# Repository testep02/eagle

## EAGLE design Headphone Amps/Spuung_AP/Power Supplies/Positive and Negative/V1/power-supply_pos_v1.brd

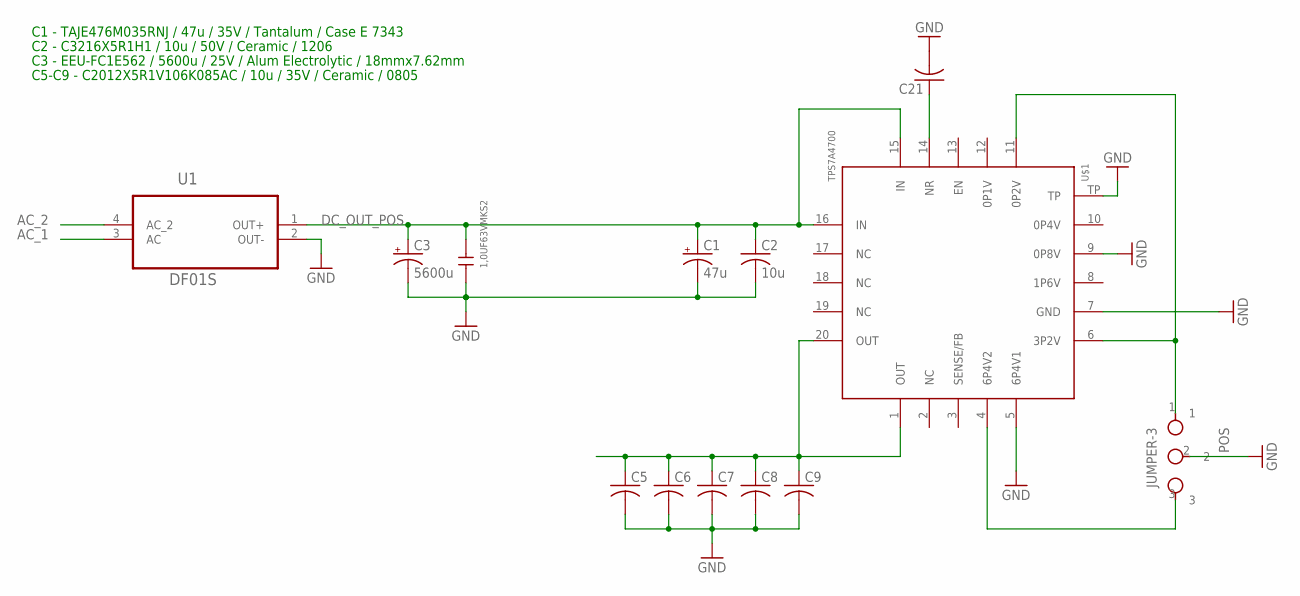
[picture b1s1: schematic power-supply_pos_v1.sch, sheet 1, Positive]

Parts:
C1: 47u; SMC_E
C2: 10u; C1206
C3: 5600u; E7,5-18
C4: 1,0UF63VMKS2; 5,0X10,0RM5,0
C5, C6, C7, C8, C9: C-USC0805; C0805
C21: C-USC0603; C0603
POS: JUMPER-3; 1X03
U1: DF01S; SOT508P985X260-4N
U$1: TPS7A4700; VQFN-20

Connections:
AC_1: U1.3 (AC)
AC_2: U1.4 (AC_2)
DC_OUT_POS: C1.+, C2.1, C3.+, C4.2, U1.1 (OUT+), U$1.15 (IN), U$1.16 (IN)
GND: C1.-, C2.2, C3.-, C4.1, C5.2, C6.2, C7.2, C8.2, C9.2, C21.2, POS.2, U1.2 (OUT-), U$1.5 (6P4V1), U$1.7 (GND), U$1.9 (0P8V), U$1.TP; also elsewhere on the board
unnamed: POS.3, U$1.4 (6P4V2)
unnamed: POS.1, U$1.6 (3P2V), U$1.11 (0P2V)
unnamed: C21.1, U$1.14 (NR)
POS_OUT: C5.1, C6.1, C7.1, C8.1, C9.1, U$1.1 (OUT), U$1.20 (OUT)

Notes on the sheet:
C1 - TAJE476M035RNJ / 47u / 35V / Tantalum / Case E 7343
C2 - C3216X5R1H1 / 10u / 50V / Ceramic / 1206
C3 - EEU-FC1E562 / 5600u / 25V / Alum Electrolytic / 18mmx7.62mm
C5-C9 - C2012X5R1V106K085AC / 10u / 35V / Ceramic / 0805

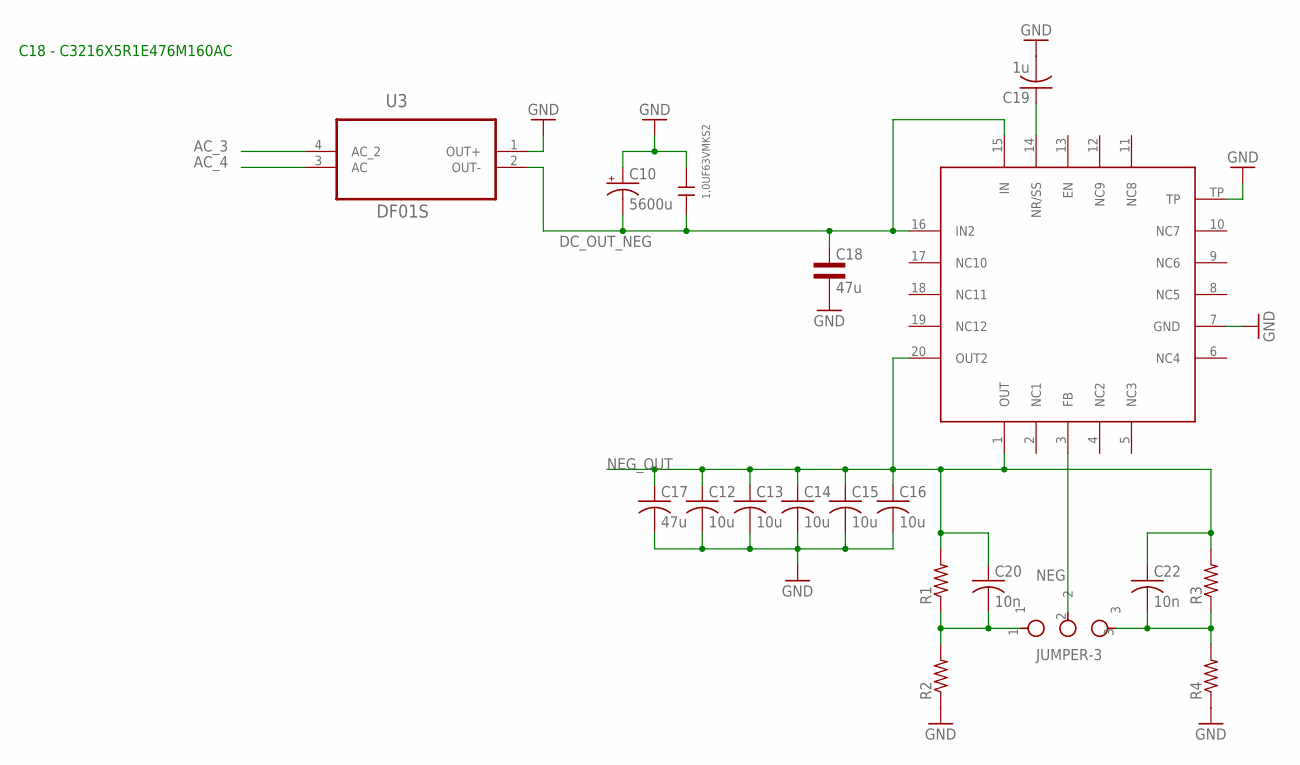
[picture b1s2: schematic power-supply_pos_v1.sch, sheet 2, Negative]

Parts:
C10: 5600u; E7,5-18
C11: 1,0UF63VMKS2; 5,0X10,0RM5,0
C12, C13, C14, C15, C16: 10u; C0805
C17: 47u; C2220K
C18: 47u; 1206L3
C19: 1u; C0603
C20, C22: 10n; C0603
NEG: JUMPER-3; 1X03
R1, R2, R3, R4: R-US_R0603; R0603
U3: DF01S; SOT508P985X260-4N
U$2: TPS7A3301RGWT; VQFN-20

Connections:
AC_3: U3.4 (AC_2)
AC_4: U3.3 (AC)
DC_OUT_NEG: C10.-, C11.1, C18.1, U3.2 (OUT-), U$2.15 (IN), U$2.16 (IN2)
GND: C10.+, C11.2, C12.2, C13.2, C14.2, C15.2, C16.2, C17.2, C18.2, C19.2, R2.1, R4.1, U3.1 (OUT+), U$2.7 (GND), U$2.TP; also elsewhere on the board
unnamed: C20.2, NEG.1, R1.1, R2.2
unnamed: C19.1, U$2.14 (NR/SS)
unnamed: C22.2, NEG.3, R3.1, R4.2
unnamed: NEG.2, U$2.3 (FB)
NEG_OUT: C12.1, C13.1, C14.1, C15.1, C16.1, C17.1, C20.1, C22.1, R1.2, R3.2, U$2.1 (OUT), U$2.20 (OUT2)

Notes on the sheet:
C18 - C3216X5R1E476M160AC

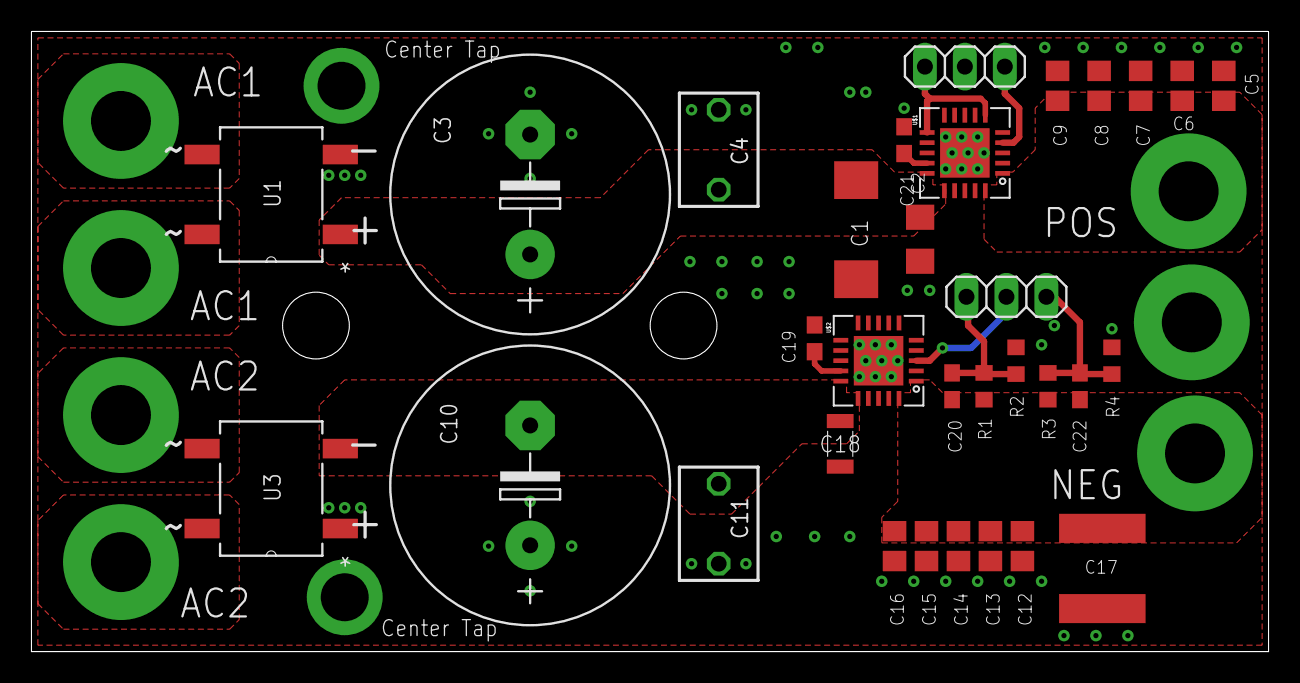
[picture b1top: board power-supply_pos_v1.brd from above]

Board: 2 copper layers, 78.6 x 39.4 mm, 32 parts (0 on the bottom side), 12 nets.

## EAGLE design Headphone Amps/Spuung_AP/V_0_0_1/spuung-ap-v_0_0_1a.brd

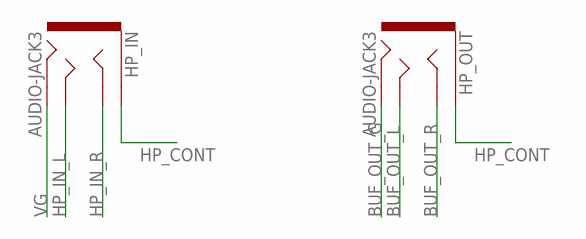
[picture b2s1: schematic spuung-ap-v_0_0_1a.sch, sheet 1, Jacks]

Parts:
HP_IN: AUDIO-JACK3; AUDIO-JACK-TRRS-SMD
HP_OUT: AUDIO-JACK3; AUDIO-JACK-TRRS-SMD

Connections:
BUF_OUT_G: HP_OUT.RING2
BUF_OUT_L: HP_OUT.TIP; also elsewhere on the board
BUF_OUT_R: HP_OUT.RING1; also elsewhere on the board
HP_CONT: HP_IN.EARTH, HP_OUT.EARTH
HP_IN_L: HP_IN.TIP; also elsewhere on the board
HP_IN_R: HP_IN.RING1; also elsewhere on the board
VG: HP_IN.RING2; also elsewhere on the board

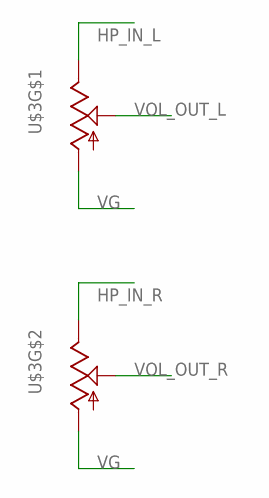
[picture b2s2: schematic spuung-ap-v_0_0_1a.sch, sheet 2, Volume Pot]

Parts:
U$3: ALPS_BLUE; ALPS_RK27

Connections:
HP_IN_L: U$3.I1 (3); also elsewhere on the board
HP_IN_R: U$3.I2 (3); also elsewhere on the board
VG: U$3.G1 (1), U$3.G2 (1); also elsewhere on the board
VOL_OUT_L: U$3.O1 (2); also elsewhere on the board
VOL_OUT_R: U$3.O2 (2); also elsewhere on the board

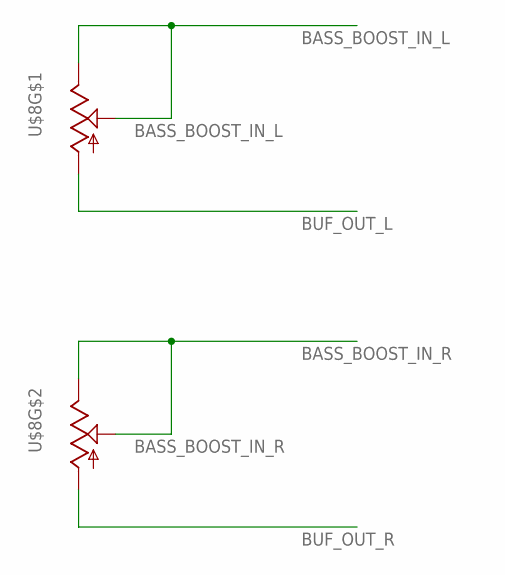
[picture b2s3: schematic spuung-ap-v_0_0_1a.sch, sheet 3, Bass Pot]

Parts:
U$8: ALPS_BLUE; ALPS_RK27

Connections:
BASS_BOOST_IN_L: U$8.I1 (3), U$8.O1 (2); also elsewhere on the board
BASS_BOOST_IN_R: U$8.I2 (3), U$8.O2 (2); also elsewhere on the board
BUF_OUT_L: U$8.G1 (1); also elsewhere on the board
BUF_OUT_R: U$8.G2 (1); also elsewhere on the board

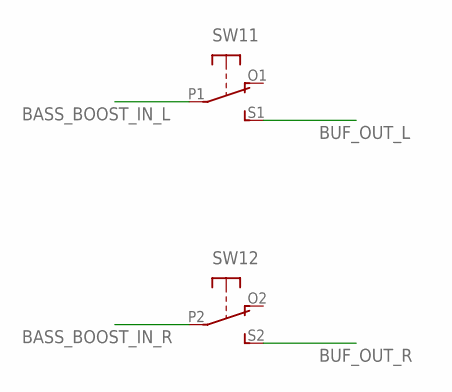
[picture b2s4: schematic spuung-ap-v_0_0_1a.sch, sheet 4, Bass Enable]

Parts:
SW1: DPDT-EG1390; EG1390

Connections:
BASS_BOOST_IN_L: SW1.P1; also elsewhere on the board
BASS_BOOST_IN_R: SW1.P2; also elsewhere on the board
BUF_OUT_L: SW1.S1 (S); also elsewhere on the board
BUF_OUT_R: SW1.S2 (S); also elsewhere on the board

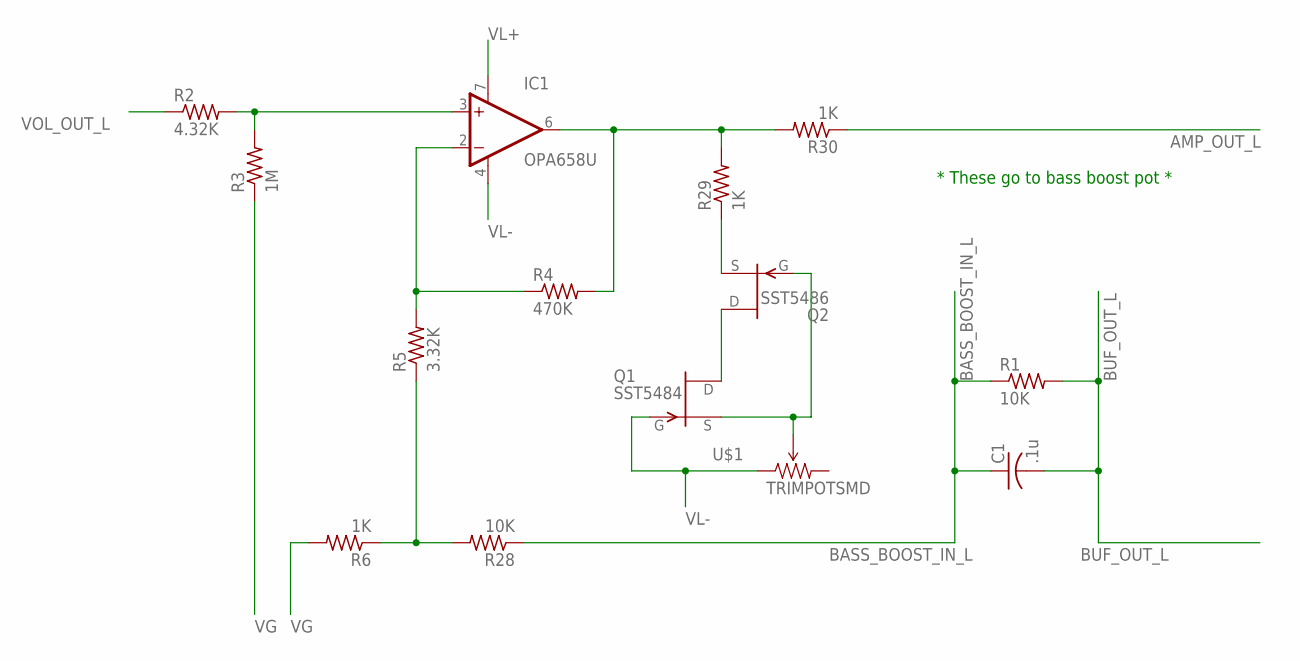
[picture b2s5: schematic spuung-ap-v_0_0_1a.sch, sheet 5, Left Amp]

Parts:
C1: .1u; C0805
IC1: OPA658U; SO08
Q1: SST5484; SOT23
Q2: SST5486; SOT23
R1, R28: 10K; R0805
R2: 4.32K; R0805
R3: 1M; R0805
R4: 470K; R0805
R5: 3.32K; R0805
R6, R29, R30: 1K; R0805
U$1: TRIMPOTSMD; TRIMPOT-3MM

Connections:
AMP_OUT_L: R30.1
BASS_BOOST_IN_L: C1.1, R1.1, R28.1; also elsewhere on the board
BUF_OUT_L: C1.2, R1.2; also elsewhere on the board
unnamed: Q2.2 (S), R29.1
unnamed: IC1.3 (+IN), R2.2, R3.2
unnamed: IC1.2 (-IN), R4.1, R5.2
unnamed: Q1.1 (D), Q2.1 (D)
unnamed: Q1.2 (S), Q2.3 (G), U$1.2 (WIPER)
unnamed: IC1.6 (OUT), R4.2, R29.2, R30.2
unnamed: R5.1, R6.1, R28.2
VG: R3.1, R6.2; also elsewhere on the board
VL+: IC1.7 (V+)
VL-: IC1.4 (V-), Q1.3 (G), U$1.1 (CCW)
VOL_OUT_L: R2.1; also elsewhere on the board

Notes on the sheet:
* These go to bass boost pot *

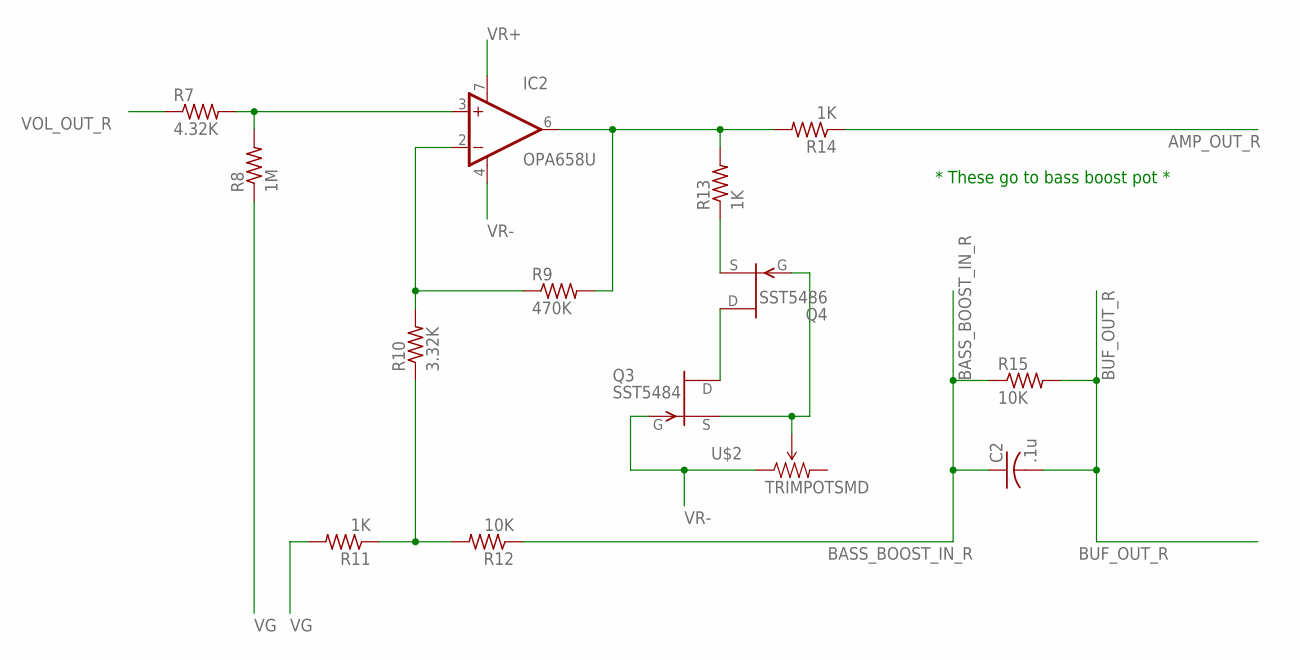
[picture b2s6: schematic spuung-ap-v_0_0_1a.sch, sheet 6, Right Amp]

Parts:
C2: .1u; C0805
IC2: OPA658U; SO08
Q3: SST5484; SOT23
Q4: SST5486; SOT23
R7: 4.32K; R0805
R8: 1M; R0805
R9: 470K; R0805
R10: 3.32K; R0805
R11, R13, R14: 1K; R0805
R12, R15: 10K; R0805
U$2: TRIMPOTSMD; TRIMPOT-3MM

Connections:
AMP_OUT_R: R14.1
BASS_BOOST_IN_R: C2.1, R12.1, R15.1; also elsewhere on the board
BUF_OUT_R: C2.2, R15.2; also elsewhere on the board
unnamed: IC2.3 (+IN), R7.2, R8.2
unnamed: IC2.2 (-IN), R9.1, R10.2
unnamed: IC2.6 (OUT), R9.2, R13.2, R14.2
unnamed: R10.1, R11.1, R12.2
unnamed: Q4.2 (S), R13.1
unnamed: Q3.1 (D), Q4.1 (D)
unnamed: Q3.2 (S), Q4.3 (G), U$2.2 (WIPER)
VG: R8.1, R11.2; also elsewhere on the board
VOL_OUT_R: R7.1; also elsewhere on the board
VR+: IC2.7 (V+)
VR-: IC2.4 (V-), Q3.3 (G), U$2.1 (CCW)

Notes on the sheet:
* These go to bass boost pot *

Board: 2 copper layers, 33 parts (0 on the bottom side), 26 nets, no tracks yet.

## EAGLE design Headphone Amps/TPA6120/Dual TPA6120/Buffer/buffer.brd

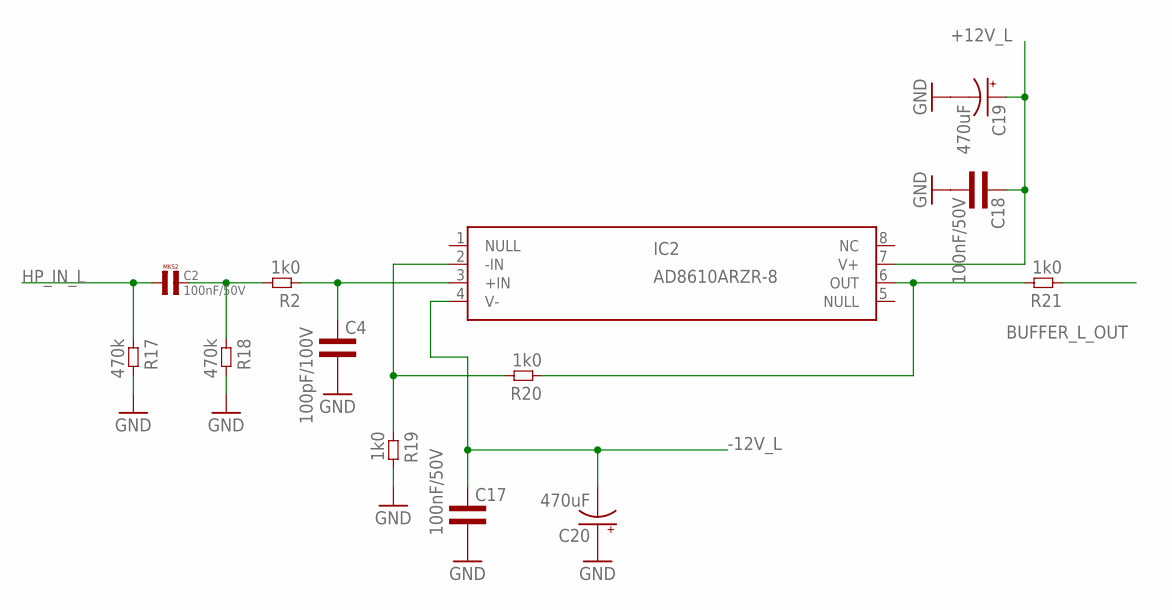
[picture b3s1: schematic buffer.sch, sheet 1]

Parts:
C2: 100nF/50V; R5B3
C4: 100pF/100V; 0603L3
C17, C18: 100nF/50V; 0603L3
C19, C20: 470uF; E3,5-8
IC2: AD8610ARZR-8; 8-LEAD-SOIC_N
R2, R19, R20, R21: 1k0; 0603L3
R17, R18: 470k; 0603L3

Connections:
+12V_L: C18.P$1 (1), C19.+, IC2.7 (V+); also elsewhere on the board
-12V_L: C17.P$1 (1), C20.-, IC2.4 (V-); also elsewhere on the board
BUFFER_L_OUT: IC2.6 (OUT), R20.P$1 (1), R21.P$2 (2)
BUFF_L_OUT: R21.P$1 (1); also elsewhere on the board
GND: C4.P$2 (2), C17.P$2 (2), C18.P$2 (2), C19.-, C20.+, R17.P$2 (2), R18.P$2 (2), R19.P$2 (2); also elsewhere on the board
HP_IN_L: C2.1, R17.P$1 (1); also elsewhere on the board
unnamed: C2.2, R2.P$2 (2), R18.P$1 (1)
unnamed: C4.P$1 (1), IC2.3 (+IN), R2.P$1 (1)
unnamed: IC2.2 (-IN), R19.P$1 (1), R20.P$2 (2)

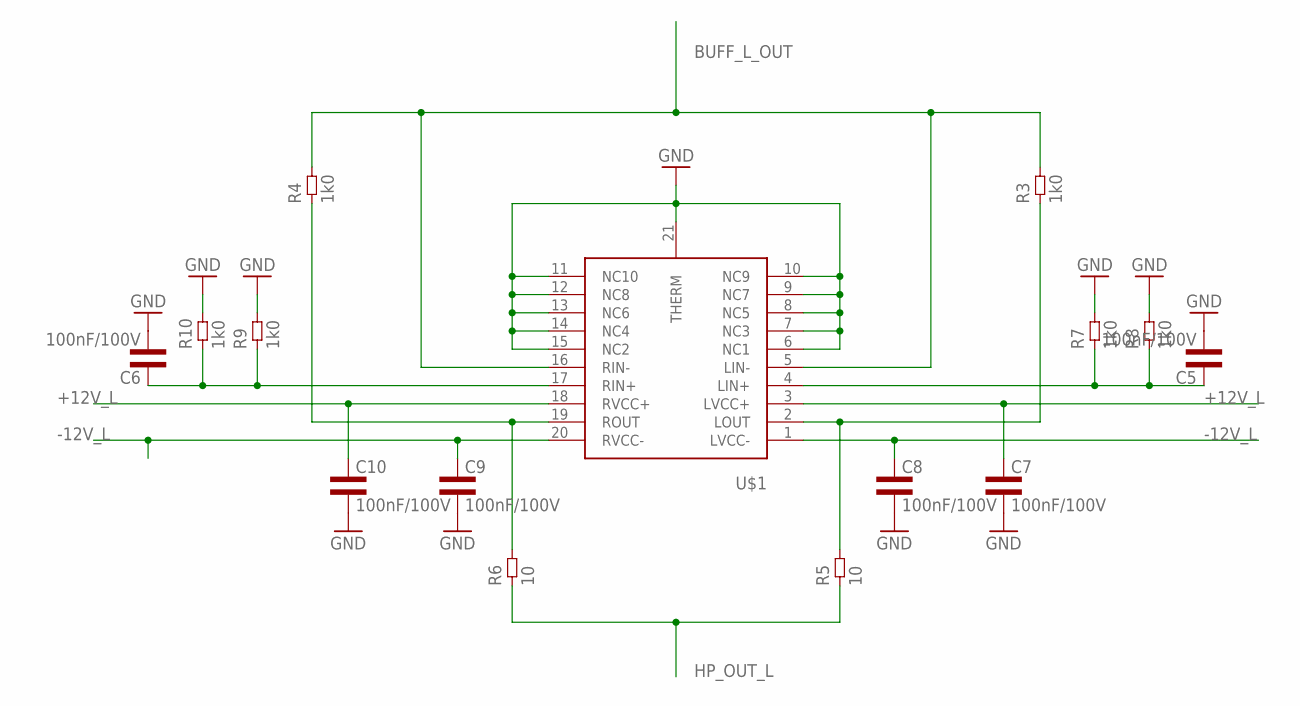
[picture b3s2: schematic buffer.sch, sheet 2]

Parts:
C5, C6: 100nF/100V; 0603L3
C7, C8, C9, C10: 100nF/100V; 0805L3
R3, R4, R7, R8, R9, R10: 1k0; 0603L3
R5, R6: 10; 1210L3
U$1: TPA6120_TPA6120

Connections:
+12V_L: C7.1, C10.1, U$1.3 (LVCC+), U$1.18 (RVCC+); also elsewhere on the board
-12V_L: C8.1, C9.1, U$1.1 (LVCC-), U$1.20 (RVCC-); also elsewhere on the board
BUFF_L_OUT: R3.P$2 (2), R4.P$2 (2), U$1.5 (LIN-), U$1.16 (RIN-); also elsewhere on the board
GND: C5.P$2 (2), C6.P$2 (2), C7.2, C8.2, C9.2, C10.2, R7.P$2 (2), R8.P$2 (2), R9.P$2 (2), R10.P$2 (2), U$1.6 (NC1), U$1.7 (NC3), U$1.8 (NC5), U$1.9 (NC7), U$1.10 (NC9), U$1.11 (NC10), U$1.12 (NC8), U$1.13 (NC6), U$1.14 (NC4), U$1.15 (NC2), U$1.21 (THERM); also elsewhere on the board
HP_OUT_L: R5.P$1 (1), R6.P$1 (1); also elsewhere on the board
unnamed: C5.P$1 (1), R7.P$1 (1), R8.P$1 (1), U$1.4 (LIN+)
unnamed: C6.P$1 (1), R9.P$1 (1), R10.P$1 (1), U$1.17 (RIN+)
OUT_L: R3.P$1 (1), R5.P$2 (2), U$1.2 (LOUT)
OUT_R: R4.P$1 (1), R6.P$2 (2), U$1.19 (ROUT)

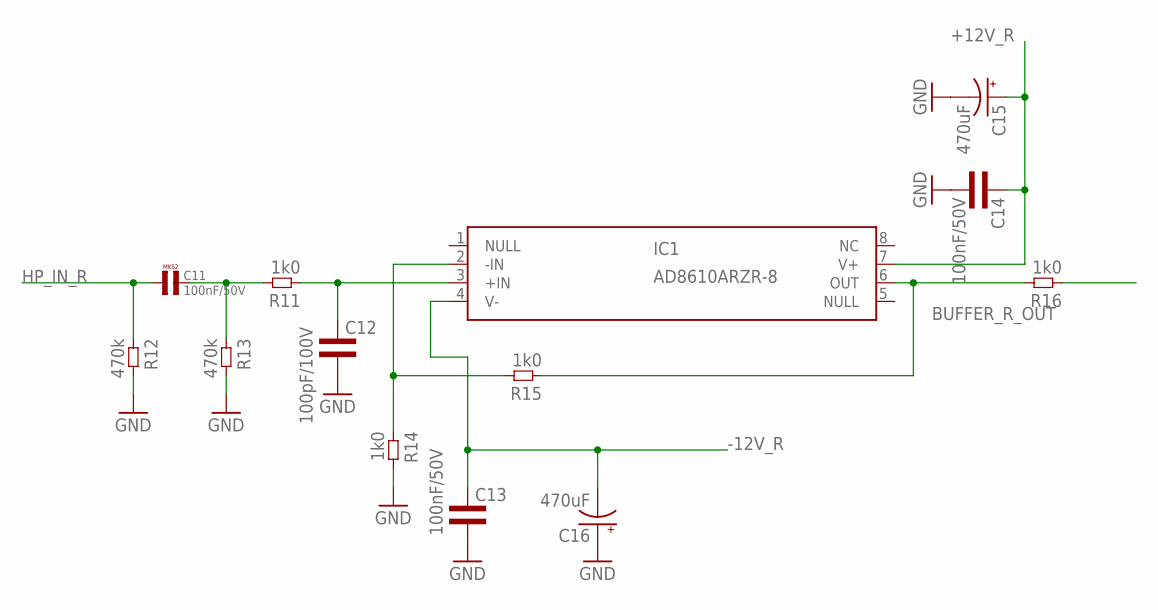
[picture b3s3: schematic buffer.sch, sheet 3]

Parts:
C11: 100nF/50V; R5B3
C12: 100pF/100V; 0603L3
C13, C14: 100nF/50V; 0603L3
C15, C16: 470uF; E3,5-8
IC1: AD8610ARZR-8; 8-LEAD-SOIC_N
R11, R14, R15, R16: 1k0; 0603L3
R12, R13: 470k; 0603L3

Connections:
+12V_R: C14.P$1 (1), C15.+, IC1.7 (V+); also elsewhere on the board
-12V_R: C13.P$1 (1), C16.-, IC1.4 (V-); also elsewhere on the board
BUFFER_R_OUT: IC1.6 (OUT), R15.P$1 (1), R16.P$2 (2)
BUFF_R_OUT: R16.P$1 (1); also elsewhere on the board
GND: C12.P$2 (2), C13.P$2 (2), C14.P$2 (2), C15.-, C16.+, R12.P$2 (2), R13.P$2 (2), R14.P$2 (2); also elsewhere on the board
HP_IN_R: C11.1, R12.P$1 (1); also elsewhere on the board
unnamed: C11.2, R11.P$2 (2), R13.P$1 (1)
unnamed: C12.P$1 (1), IC1.3 (+IN), R11.P$1 (1)
unnamed: IC1.2 (-IN), R14.P$1 (1), R15.P$2 (2)

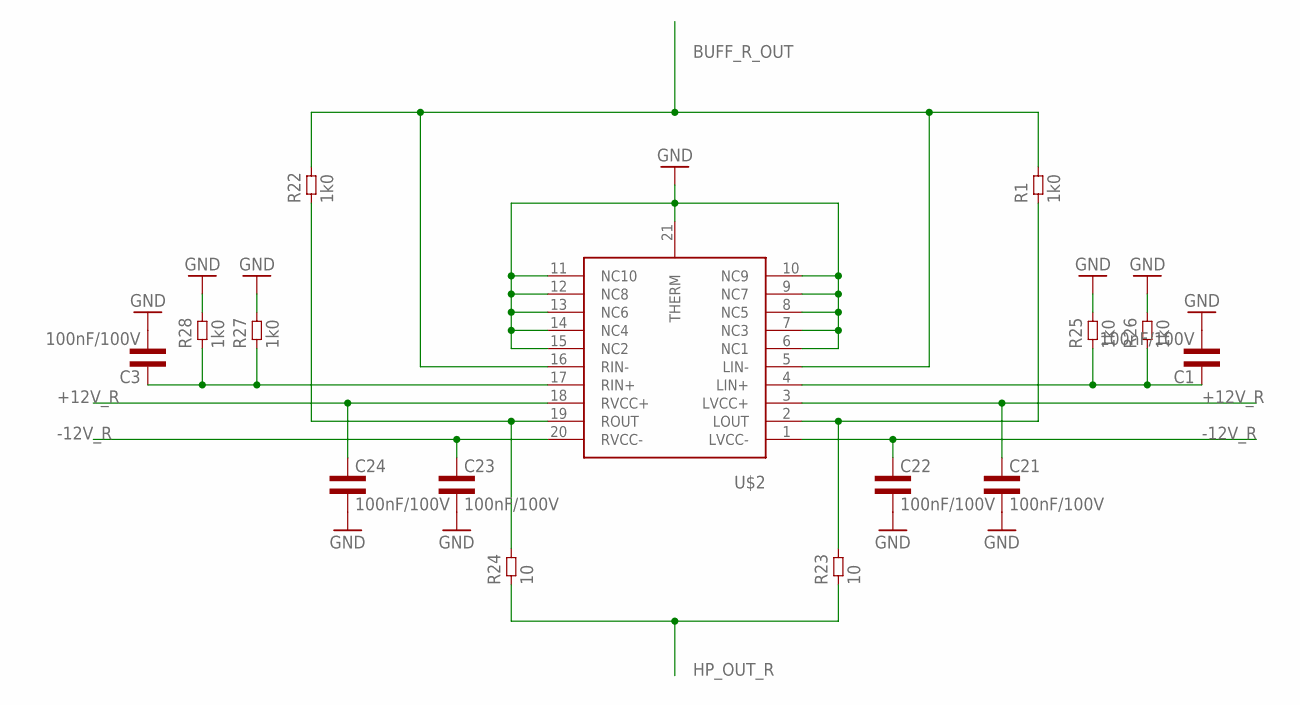
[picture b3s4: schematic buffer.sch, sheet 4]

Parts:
C1, C3: 100nF/100V; 0603L3
C21, C22, C23, C24: 100nF/100V; 0805L3
R1, R22, R25, R26, R27, R28: 1k0; 0603L3
R23, R24: 10; 1210L3
U$2: TPA6120_TPA6120

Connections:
+12V_R: C21.1, C24.1, U$2.3 (LVCC+), U$2.18 (RVCC+); also elsewhere on the board
-12V_R: C22.1, C23.1, U$2.1 (LVCC-), U$2.20 (RVCC-); also elsewhere on the board
BUFF_R_OUT: R1.P$2 (2), R22.P$2 (2), U$2.5 (LIN-), U$2.16 (RIN-); also elsewhere on the board
GND: C1.P$2 (2), C3.P$2 (2), C21.2, C22.2, C23.2, C24.2, R25.P$2 (2), R26.P$2 (2), R27.P$2 (2), R28.P$2 (2), U$2.6 (NC1), U$2.7 (NC3), U$2.8 (NC5), U$2.9 (NC7), U$2.10 (NC9), U$2.11 (NC10), U$2.12 (NC8), U$2.13 (NC6), U$2.14 (NC4), U$2.15 (NC2), U$2.21 (THERM); also elsewhere on the board
HP_OUT_R: R23.P$1 (1), R24.P$1 (1); also elsewhere on the board
unnamed: C1.P$1 (1), R25.P$1 (1), R26.P$1 (1), U$2.4 (LIN+)
unnamed: C3.P$1 (1), R27.P$1 (1), R28.P$1 (1), U$2.17 (RIN+)
OUT_L1: R1.P$1 (1), R23.P$2 (2), U$2.2 (LOUT)
OUT_R1: R22.P$1 (1), R24.P$2 (2), U$2.19 (ROUT)

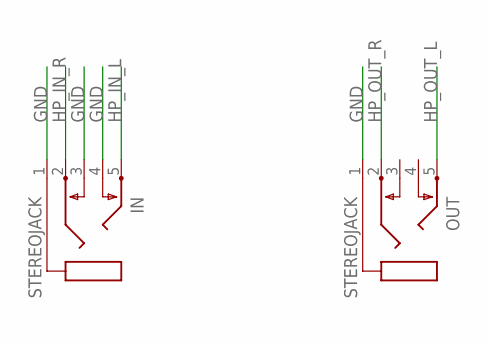
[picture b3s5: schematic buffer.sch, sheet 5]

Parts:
IN: STEREOJACK; STX3100
OUT: STEREOJACK; STX3100

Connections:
GND: IN.1, IN.3, IN.4, OUT.1; also elsewhere on the board
HP_IN_L: IN.5; also elsewhere on the board
HP_IN_R: IN.2; also elsewhere on the board
HP_OUT_L: OUT.5; also elsewhere on the board
HP_OUT_R: OUT.2; also elsewhere on the board

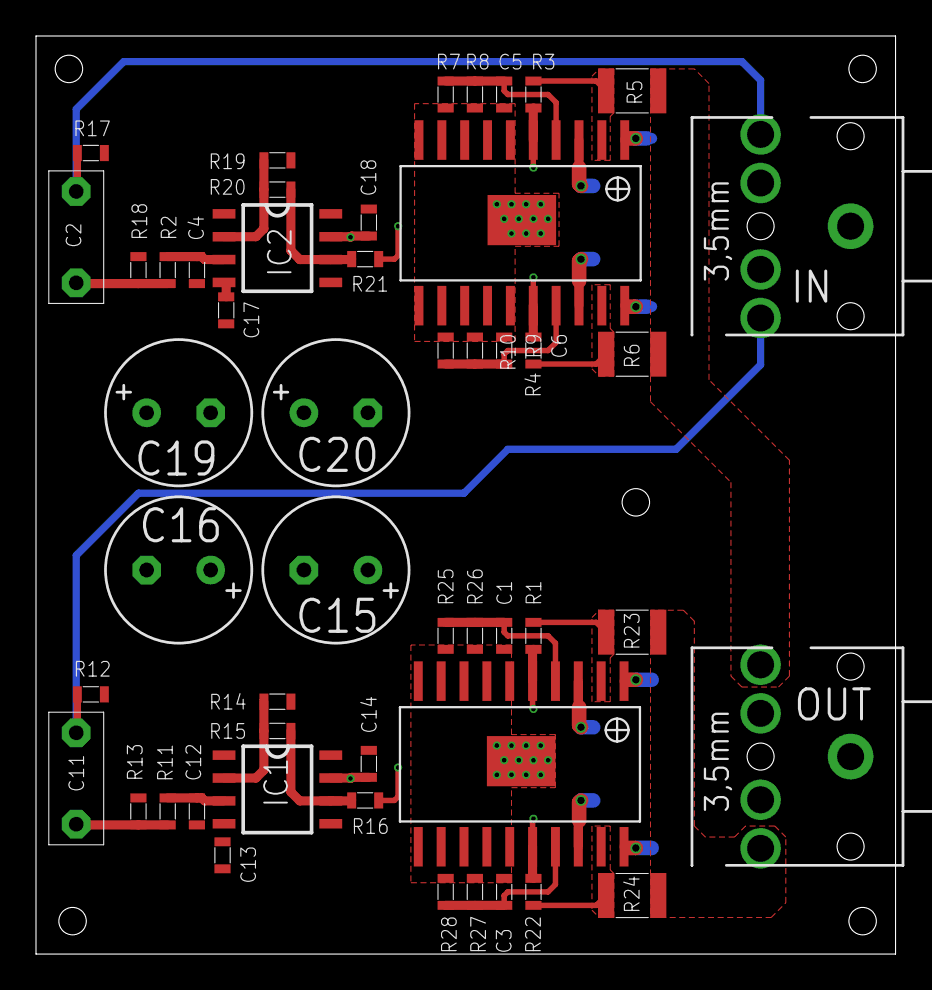
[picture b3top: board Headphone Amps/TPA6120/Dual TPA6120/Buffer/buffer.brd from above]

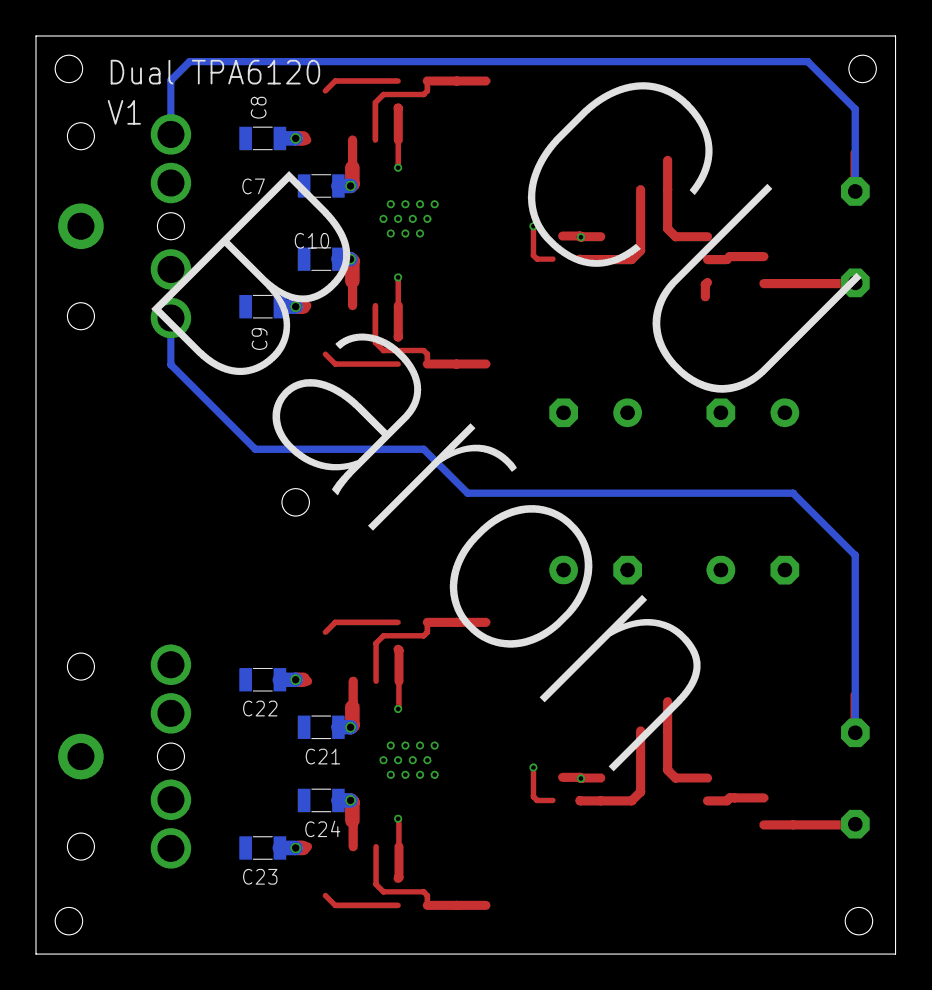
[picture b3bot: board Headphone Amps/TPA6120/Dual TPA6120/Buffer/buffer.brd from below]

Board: 4 copper layers, 47.8 x 51.0 mm, 58 parts (8 on the bottom side), 27 nets.

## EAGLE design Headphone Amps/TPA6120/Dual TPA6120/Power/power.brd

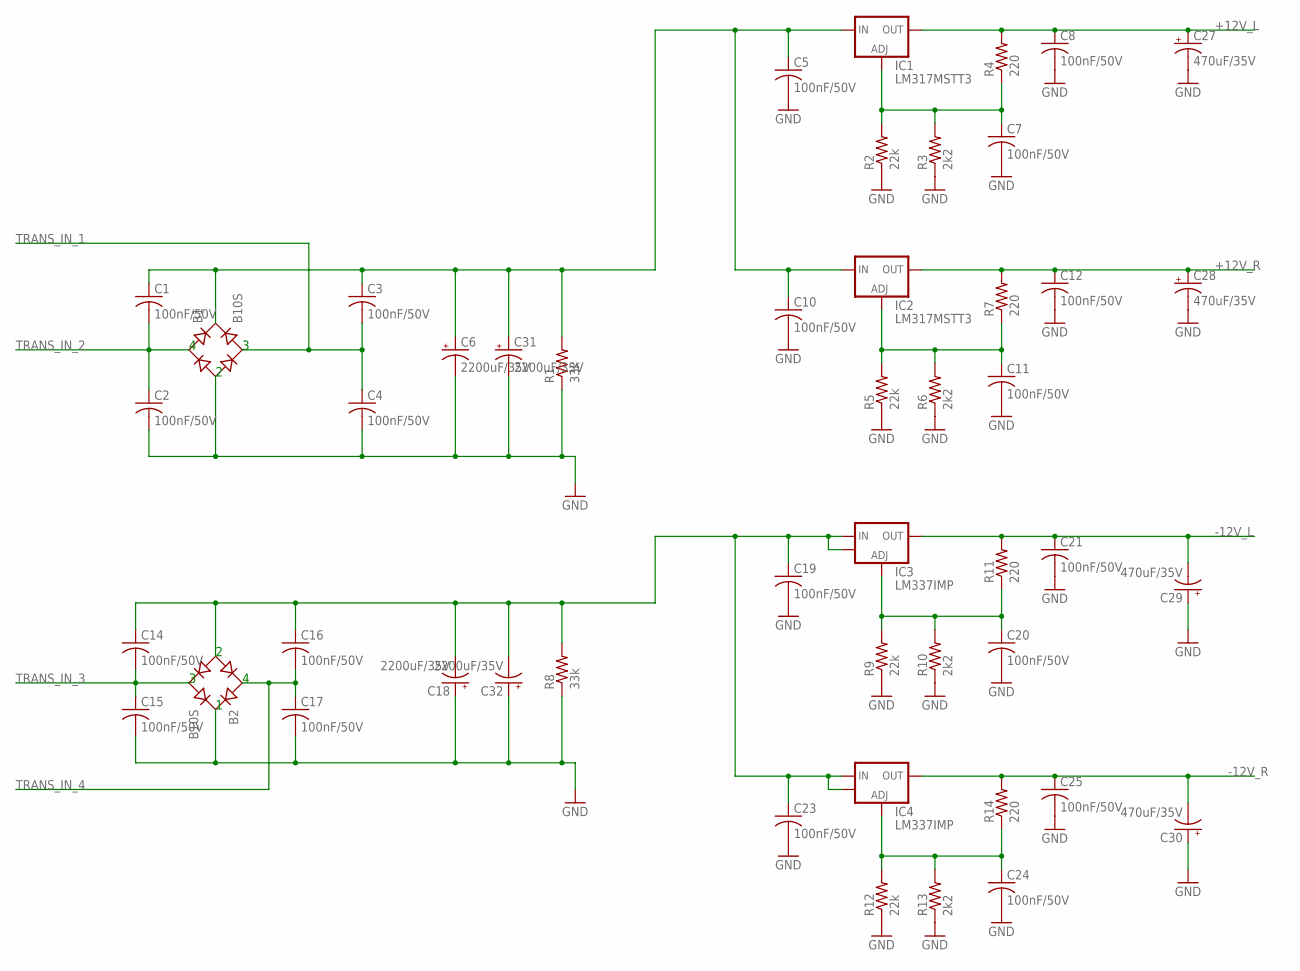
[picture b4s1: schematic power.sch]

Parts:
B1, B2: B10S; MBS
C1, C2, C3, C4, C5, C7, C8, C10, C11, C12, C14, C15, C16, C17, C19, C20, C21, C23, C24, C25: 100nF/50V; C0805
C6, C18, C31, C32: 2200uF/35V; E5-13
C27, C28, C29, C30: 470uF/35V; E5-13
IC1, IC2: LM317MSTT3; SOT223
IC3, IC4: LM337IMP; SOT-223
R1, R8: 33k; M0805
R2, R5, R9, R12: 22k; M0805
R3, R6, R10, R13: 2k2; M0805
R4, R7, R11, R14: 220; M0805

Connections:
+12V_L: C8.1, C27.+, IC1.4 (OUT), R4.2
+12V_R: C12.1, C28.+, IC2.4 (OUT), R7.2
+VSS_NOREG: B1.+, C1.1, C3.1, C5.1, C6.+, C10.1, C31.+, IC1.3 (IN), IC2.3 (IN), R1.2
-12V_L: C21.1, C29.-, IC3.3 (OUT), R11.2
-12V_R: C25.1, C30.-, IC4.3 (OUT), R14.2
-VSS_NOREG: B2.-, C14.1, C16.1, C18.-, C19.1, C23.1, C32.-, IC3.2 (IN), IC3.4, IC4.2 (IN), IC4.4, R8.2
GND: B1.-, B2.+, C2.2, C4.2, C5.2, C6.-, C7.2, C8.2, C10.2, C11.2, C12.2, C15.2, C17.2, C18.+, C19.2, C20.2, C21.2, C23.2, C24.2, C25.2, C27.-, C28.-, C29.+, C30.+, C31.-, C32.+, R1.1, R2.1, R3.1, R5.1, R6.1, R8.1, R9.1, R10.1, R12.1, R13.1
unnamed: C7.1, IC1.1 (ADJ), R2.2, R3.2, R4.1
unnamed: C11.1, IC2.1 (ADJ), R5.2, R6.2, R7.1
unnamed: C20.1, IC3.1 (ADJ), R9.2, R10.2, R11.1
unnamed: C24.1, IC4.1 (ADJ), R12.2, R13.2, R14.1
TRANS_IN_1: B1.AC2, C3.2, C4.1
TRANS_IN_2: B1.AC1, C1.2, C2.1
TRANS_IN_3: B2.AC2, C14.2, C15.1
TRANS_IN_4: B2.AC1, C16.2, C17.1

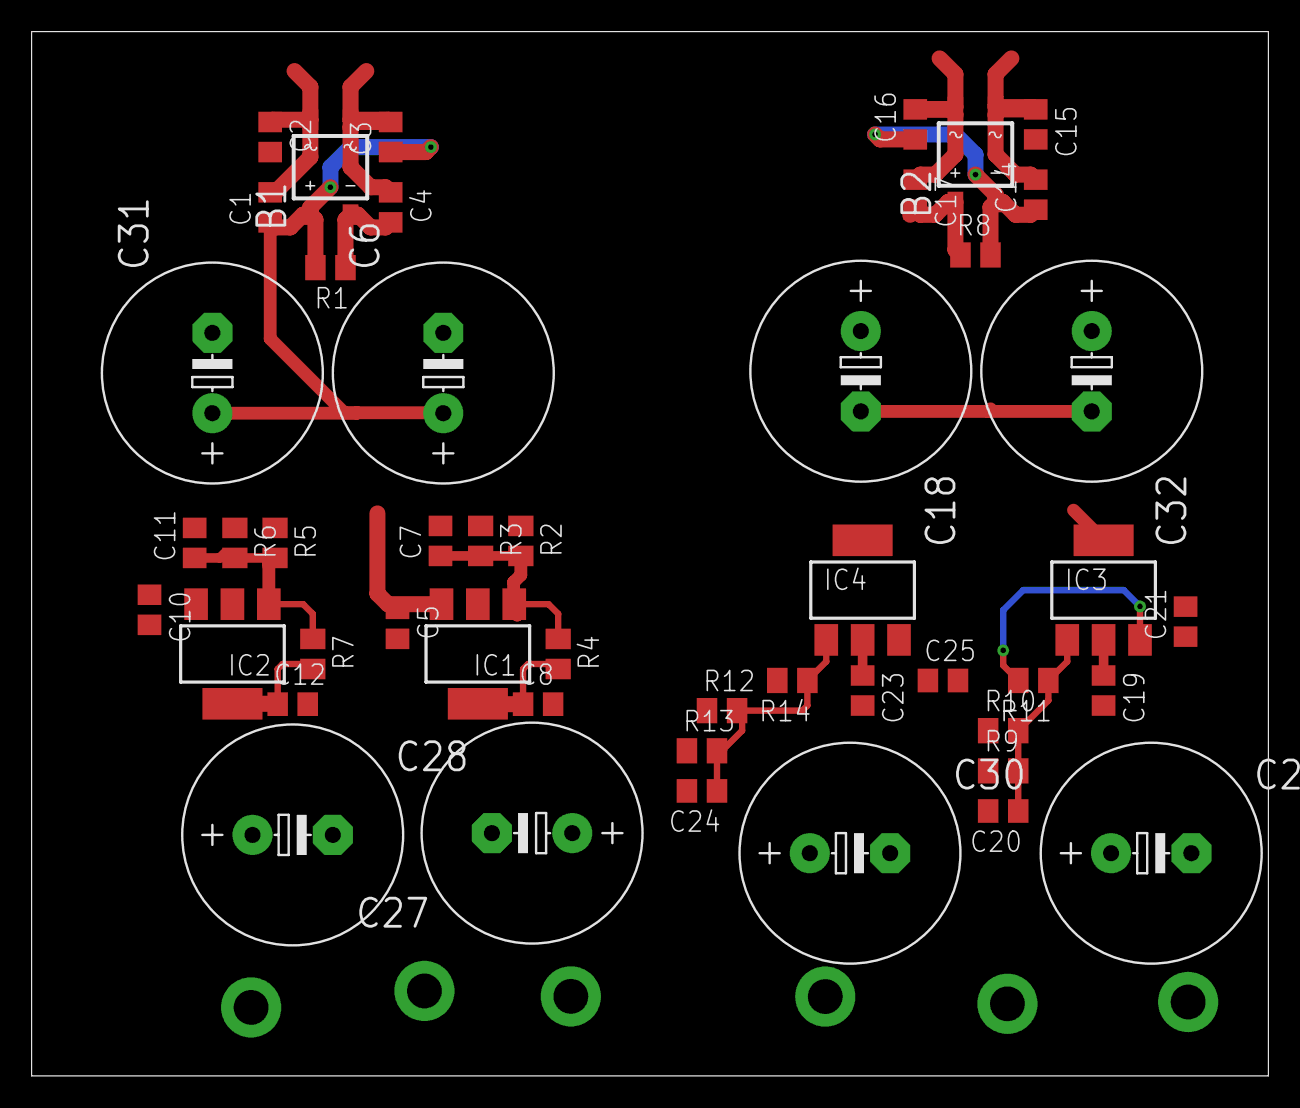
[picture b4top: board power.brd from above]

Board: 2 copper layers, 78.2 x 66.0 mm, 48 parts (0 on the bottom side), 15 nets.

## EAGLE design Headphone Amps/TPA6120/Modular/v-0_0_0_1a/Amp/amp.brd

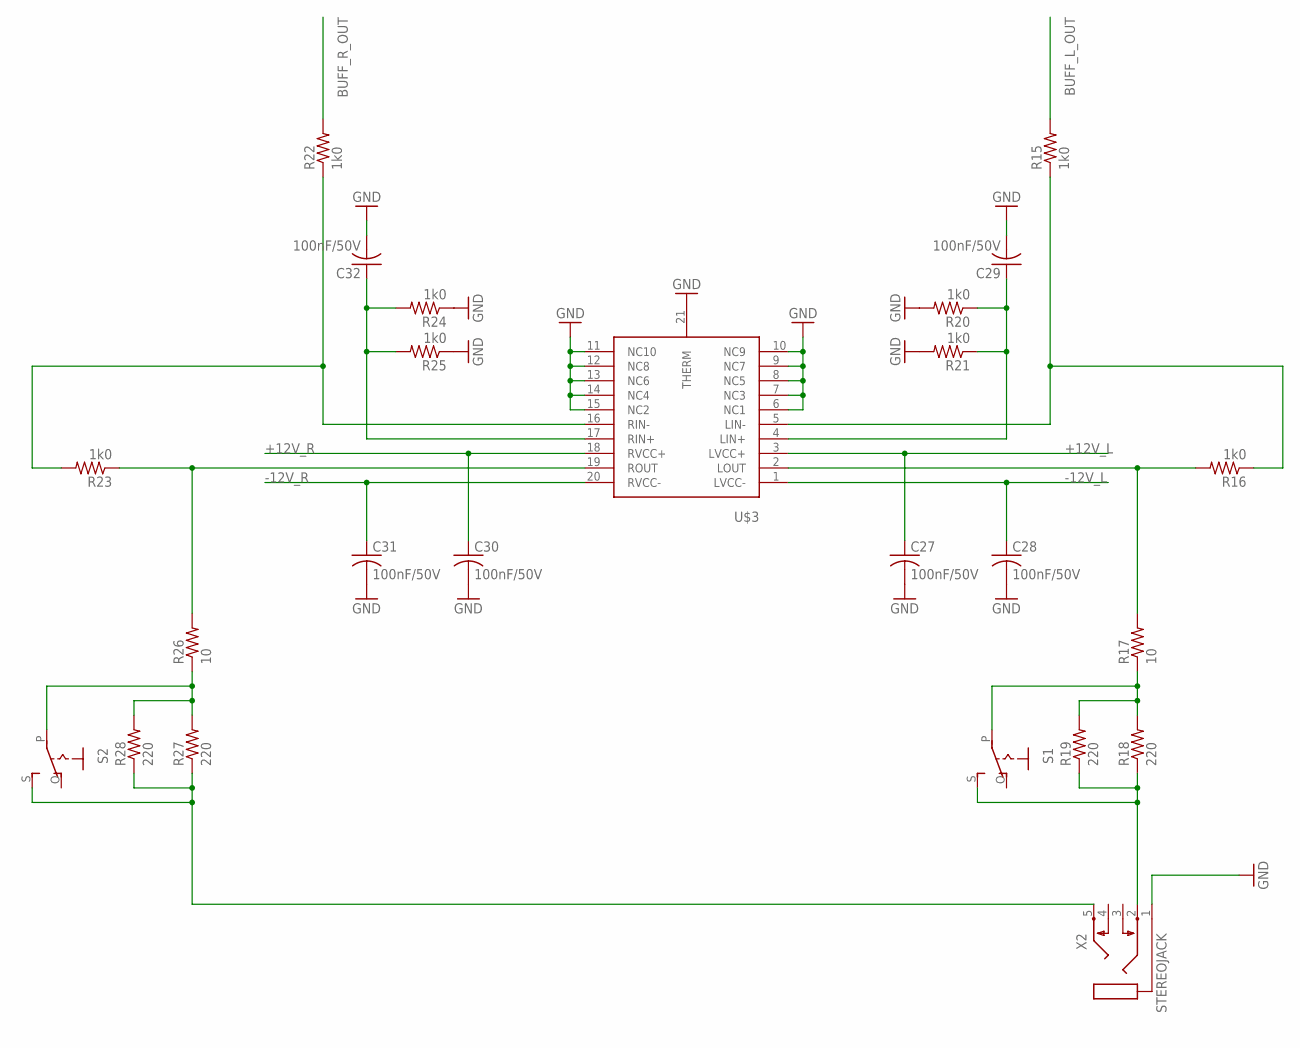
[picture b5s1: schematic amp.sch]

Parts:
C27, C28, C29, C30, C31, C32: 100nF/50V; C0805
R15, R16, R20, R21, R22, R23, R24, R25: 1k0; M0805
R17, R26: 10; M0805
R18, R19, R27, R28: 220; M0805
S1, S2: EG1218S; EG1218
U$3: TPA6120
X2: STEREOJACK; STX3100

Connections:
+12V_L: C27.1, U$3.3 (LVCC+)
+12V_R: C30.1, U$3.18 (RVCC+)
-12V_L: C28.1, U$3.1 (LVCC-)
-12V_R: C31.1, U$3.20 (RVCC-)
BUFF_L_OUT: R15.2
BUFF_R_OUT: R22.2
GND: C27.2, C28.2, C29.2, C30.2, C31.2, C32.2, R20.2, R21.2, R24.1, R25.1, U$3.6 (NC1), U$3.7 (NC3), U$3.8 (NC5), U$3.9 (NC7), U$3.10 (NC9), U$3.11 (NC10), U$3.12 (NC8), U$3.13 (NC6), U$3.14 (NC4), U$3.15 (NC2), U$3.21 (THERM), X2.1
unnamed: R15.1, R16.1, U$3.5 (LIN-)
unnamed: R16.2, R17.2, U$3.2 (LOUT)
unnamed: R17.1, R18.2, R19.2, S1.P
unnamed: R18.1, R19.1, S1.S, X2.2
unnamed: C29.1, R20.1, R21.1, U$3.4 (LIN+)
unnamed: R22.1, R23.2, U$3.16 (RIN-)
unnamed: R23.1, R26.2, U$3.19 (ROUT)
unnamed: C32.1, R24.2, R25.2, U$3.17 (RIN+)
unnamed: R26.1, R27.2, R28.2, S2.P
unnamed: R27.1, R28.1, S2.S, X2.5

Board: 2 copper layers, 24 parts (0 on the bottom side), 15 nets, no tracks yet.

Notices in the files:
parts and their libraries:
SparkFun-Connectors: Licensing: CC v3.0 Share-Alike You are welcome to use this library for commercial purposes.
